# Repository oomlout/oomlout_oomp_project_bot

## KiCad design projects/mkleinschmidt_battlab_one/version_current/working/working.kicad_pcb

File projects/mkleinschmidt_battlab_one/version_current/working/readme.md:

# Battlab-One by mkleinschmidt  
This is a harvested standardized copy of a project from github.  
The original project can be found at:  
https://github.com/mkleinschmidt/Battlab-One  
Please consult that link for additional, details, files, and license information.  
Note: It was auto harvested and if the original repo had more than one board file or anything out of the ordinary the files here are likely not representative.

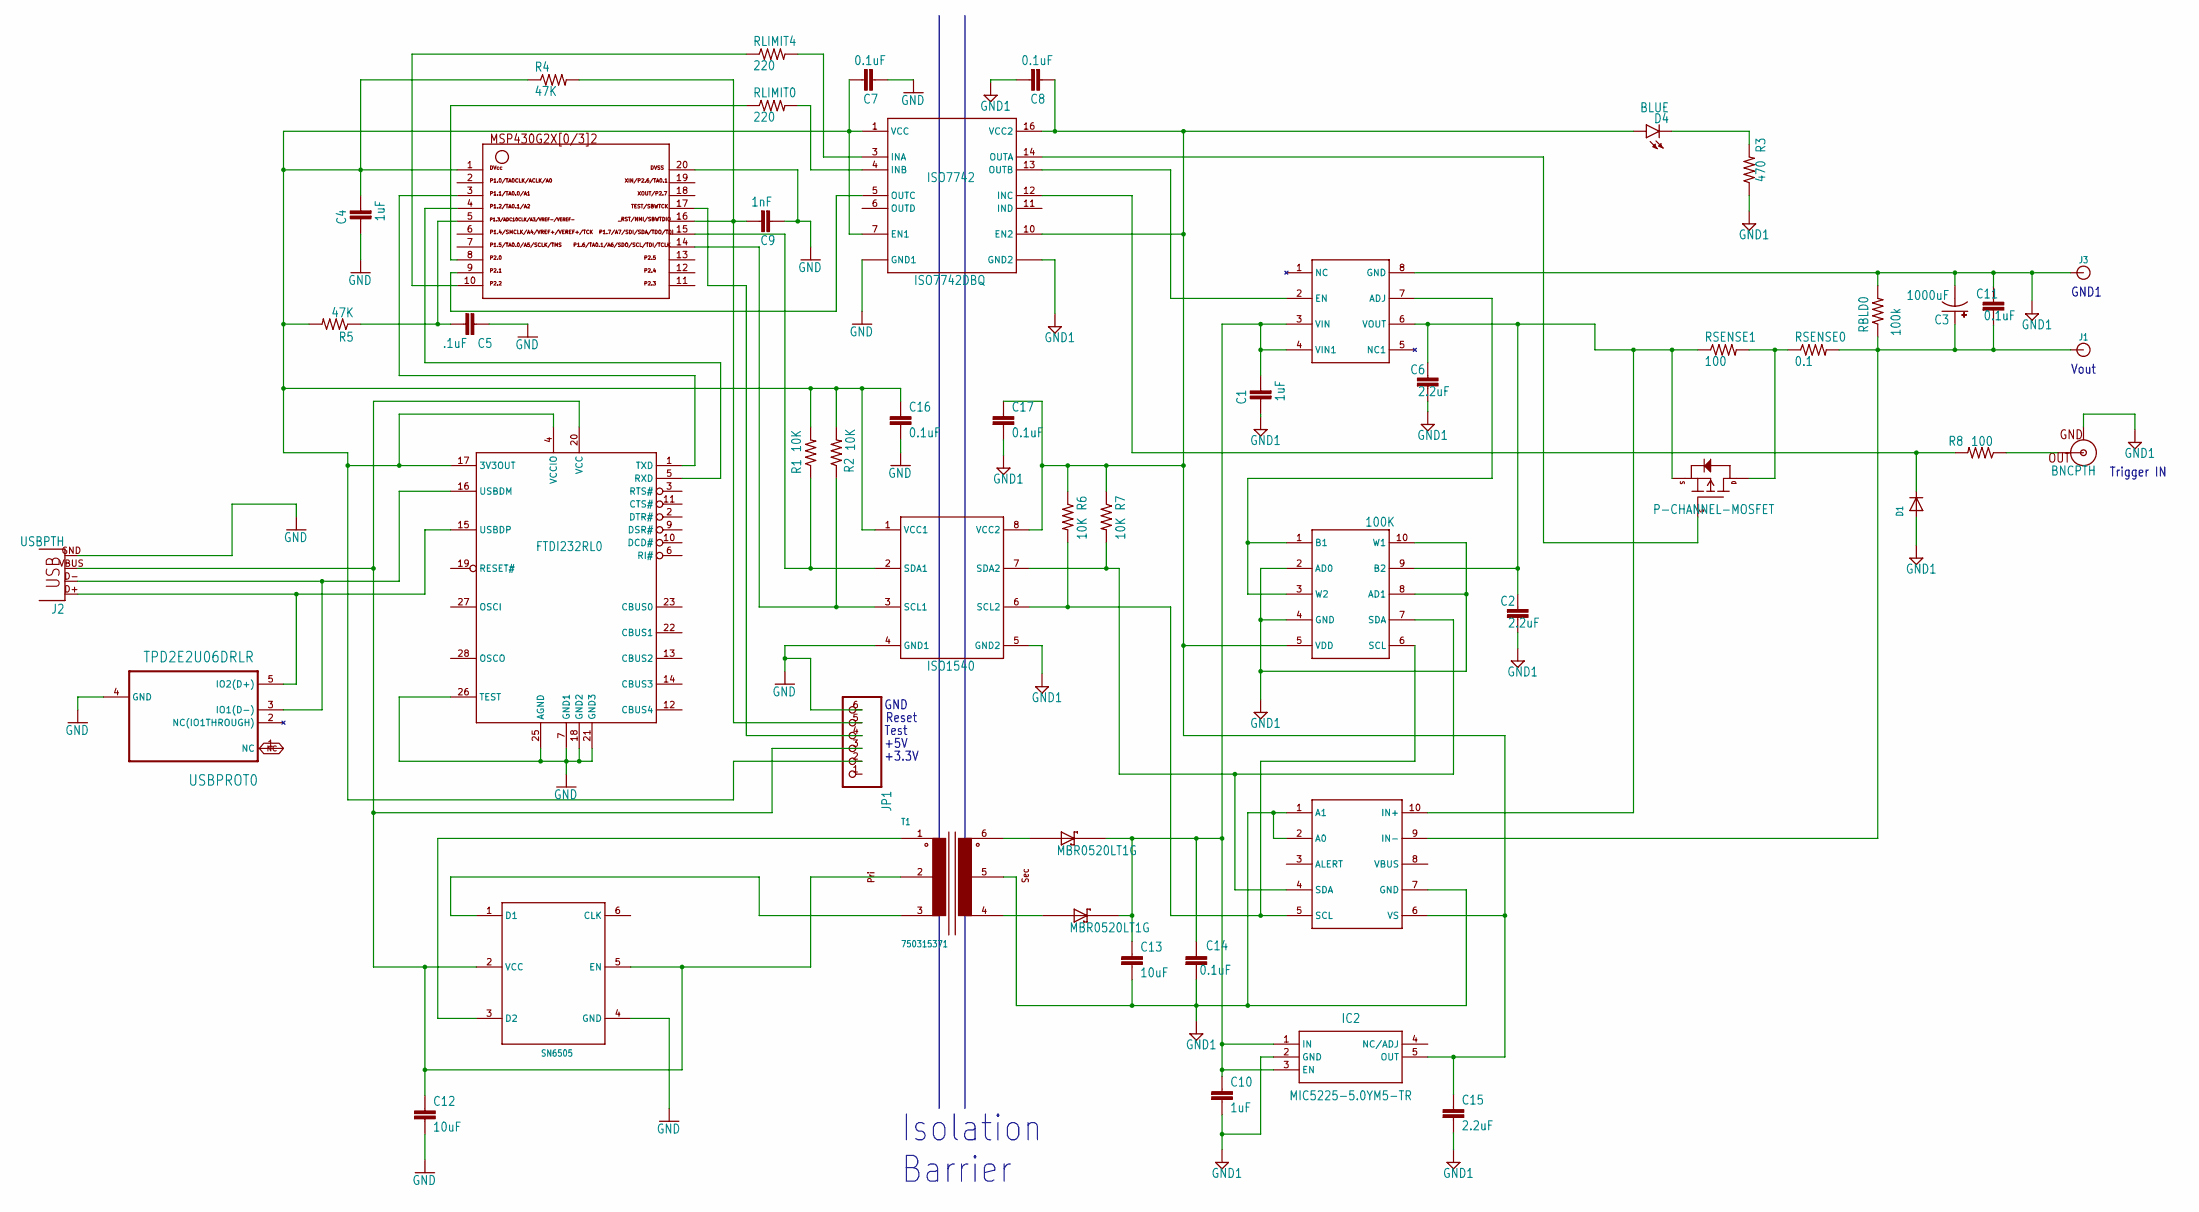
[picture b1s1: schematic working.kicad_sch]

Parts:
AD5248: 100K; MSOP-10
AP2318: AP2318; SOIC-8
C1, C4, C10: 1uF; 1206
C2, C6, C15: 2.2uF; 1206
C3: 1000uF; PANASONIC_F
C5: .1uF; 1206
C7, C8, C11, C14, C16, C17: 0.1uF; 1206
C9: 1nF; 1206
C12, C13: 10uF; 1206
D1: DIODESOD-123; SOD-123
D2, D3: MBR0520LT1G; SOD3716X117(SOD-123)
D4: BLUE; LED-1206
FTDI232RL0: FT232RL; SSOP28DB
IC2: MIC5225-5.0YM5-TR; SOT95P280X130-5N
INA233: INA233; VSSOP-10
ISO1540: ISO1540; SOIC127P600X175-8N
ISO7742: ISO7742DBQ; SOP63P599X175-16N
J1, J3: BANANA_CONN
J2: USBPTH; USB-B-PTH
JP1: PINHD-1X6; 1X06
MSP430: G2X[0/3]2---PW20; PW20
P-MOS0: P-CHANNEL-MOSFET; SOT23-3
R1, R2, R6, R7: 10K; 1206
R3: 470; 1206
R4, R5: 47K; 1206
R8: 100; 1206
RBLD0: 100k; 1206
RLIMIT0, RLIMIT4: 220; 1206
RSENSE0: 0.1; 1206
RSENSE1: 100; 1206
SN6505: SN6505; SOT95P280X145-6N
T1: 750315371; TOR-6P-HT4_SMT_6PIN_(1201)
TRIG0: BNCPTH; BNC
USBPROT0: TPD2E2U06DRLR; SOT50P160X60-5N

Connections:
3.3V: C4.2, C7.2, C16.1, FTDI232RL0.4 (VCCIO), FTDI232RL0.17 (3V3OUT), ISO1540.1 (VCC1), ISO7742.1 (VCC), ISO7742.7 (EN1), JP1.2, MSP430.1, R1.2, R2.2, R4.1, R5.2
+5V_LDO: AD5248.5 (VDD), C8.1, C15.1, C17.1, D4.A, IC2.5 (OUT), INA233.6 (VS), ISO1540.8 (VCC2), ISO7742.10 (EN2), ISO7742.16 (VCC2), R6.1, R7.1
GND: C4.1, C5.1, C7.1, C9.1, C12.2, C16.2, FTDI232RL0.7 (GND1), FTDI232RL0.18 (GND2), FTDI232RL0.21 (GND3), FTDI232RL0.25 (AGND), FTDI232RL0.26 (TEST), ISO1540.4 (GND1), ISO7742.2 (GND1), ISO7742.8 (GND1), J2.GND, JP1.6, MSP430.20, SN6505.4 (GND), USBPROT0.4 (GND)
GND1: AD5248.2 (AD0), AD5248.4 (GND), AD5248.8 (AD1), AD5248.10 (W1), AP2318.8 (GND), C1.1, C2.2, C3.-, C6.2, C8.2, C10.2, C11.1, C13.2, C14.2, C15.2, C17.2, D1.A, IC2.2 (GND), INA233.1 (A1), INA233.2 (A0), INA233.7 (GND), ISO1540.5 (GND2), ISO7742.9 (GND2), ISO7742.15 (GND2), J3.P$1, R3.1, RBLD0.2, T1.5, TRIG0.GND
LDO_EN: ISO7742.4 (INB), RLIMIT0.2
LDO_EN1: MSP430.8, RLIMIT0.1
LDO_EN2: AP2318.2 (EN), ISO7742.13 (OUTB)
unnamed: P-MOS0.3 (D), RSENSE0.1, RSENSE1.2
unnamed: AP2318.3 (VIN), AP2318.4 (VIN1), C1.2, C10.1, C13.1, C14.1, D2.1 (C), D3.1 (C), IC2.1 (IN), IC2.3 (EN)
unnamed: D3.2 (A), T1.4
unnamed: D2.2 (A), T1.6
unnamed: AD5248.1 (B1), AD5248.3 (W2), AP2318.7 (ADJ)
unnamed: D4.C, R3.2
unnamed: R8.1, TRIG0.S (OUT)
NC: USBPROT0.1 (NC)
RESET: C9.2, JP1.5, MSP430.16, R4.2
RS_EN: MSP430.10, RLIMIT4.1
RS_EN1: ISO7742.3 (INA), RLIMIT4.2
RS_EN2: ISO7742.14 (OUTA), P-MOS0.1 (G)
SCL1: ISO1540.3 (SCL1), MSP430.14, R2.1
SCL2: AD5248.6 (SCL), INA233.5 (SCL), ISO1540.6 (SCL2), R6.2
SDA1: ISO1540.2 (SDA1), MSP430.15, R1.1
SDA2: AD5248.7 (SDA), INA233.4 (SDA), ISO1540.7 (SDA2), R7.2
TEST: JP1.4, MSP430.17
TRANS1: SN6505.3 (D2), T1.1
TRANS3: SN6505.1 (D1), T1.3
TRIGGER_MSP1: ISO7742.5 (OUTC), MSP430.9
TRIGGER_MSP2: D1.C, ISO7742.12 (INC), R8.2
UART_RX: FTDI232RL0.5 (RXD), MSP430.4
UART_TX: FTDI232RL0.1 (TXD), MSP430.3
USB+: FTDI232RL0.15 (USBDP), J2.D+, USBPROT0.5 (IO2(D+))
USB-: FTDI232RL0.16 (USBDM), J2.D-, USBPROT0.3 (IO1(D-))
VBUS+5V: C12.1, FTDI232RL0.20 (VCC), J2.VBUS, JP1.3, SN6505.2 (VCC), SN6505.5 (EN), T1.2
VOUT: C3.+, C11.2, INA233.9 (IN-), J1.P$1, RBLD0.1, RSENSE0.2
VREF: C5.2, MSP430.5, R5.1
V_OUT: AD5248.9 (B2), AP2318.6 (VOUT), C2.1, C6.1, INA233.10 (IN+), P-MOS0.2 (S), RSENSE1.1

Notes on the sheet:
+5V
Reset
Trigger IN
GND
Vout
Isolation Barrier
Test
GND1
+3.3V

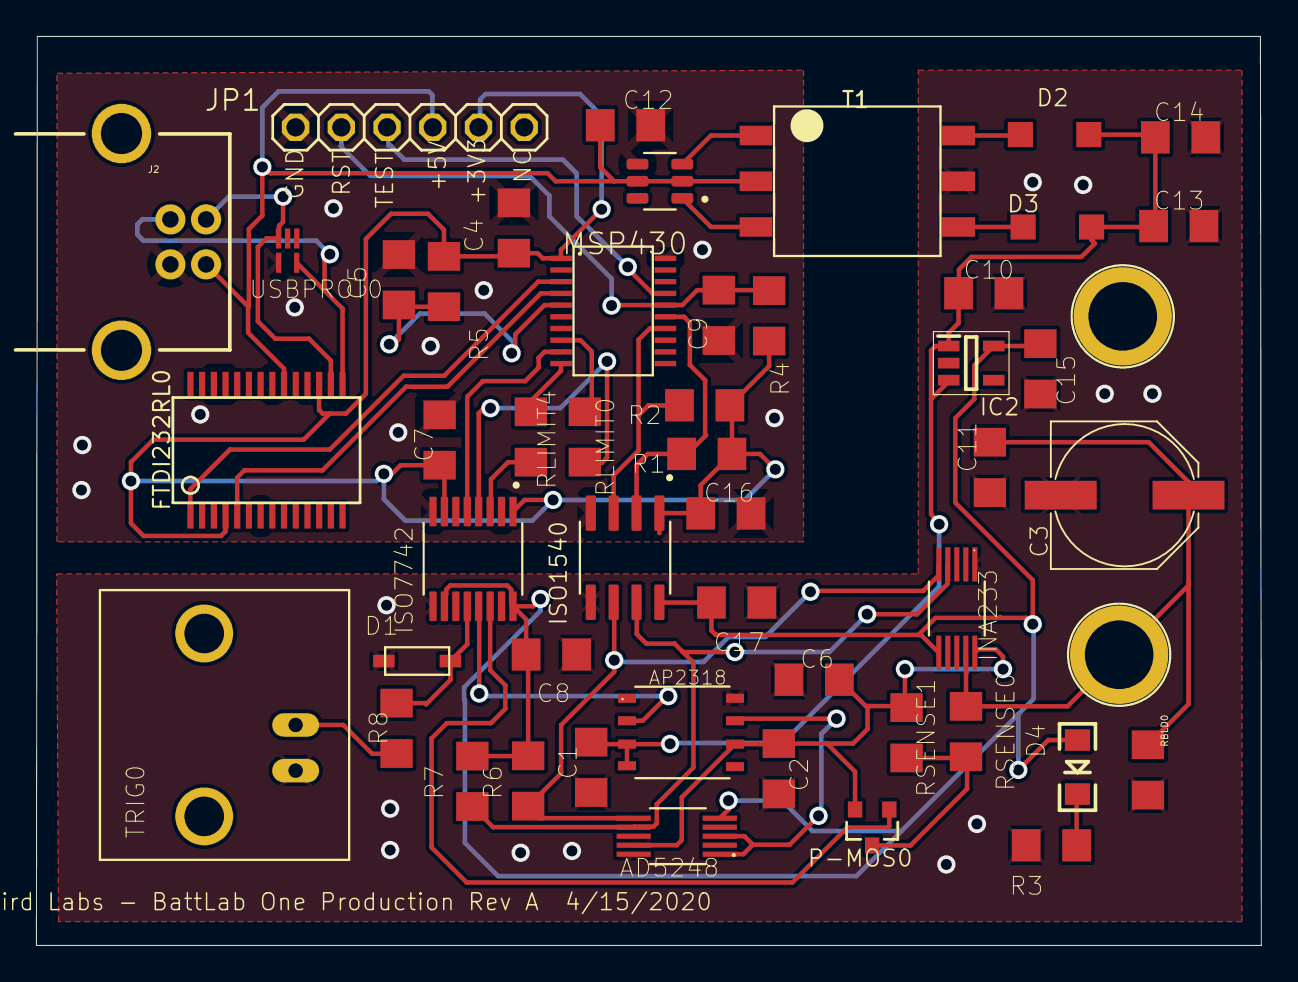
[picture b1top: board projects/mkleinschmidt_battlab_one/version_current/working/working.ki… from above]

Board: 2 copper layers, 68.1 x 50.5 mm, 51 parts (0 on the bottom side), 35 nets.

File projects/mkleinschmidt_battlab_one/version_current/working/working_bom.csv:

"Id";"Designator";"Footprint";"Quantity";"Designation";"Supplier and ref";
1;"C15,C2,C6";"1206";3;"2.2uF";;;
2;"C7,C14,C17,C8,C11,C16";"1206";6;"0.1uF";;;
3;"R8";"1206";1;"100";;;
4;"ISO1540";"SOIC127P600X175-8N";1;"ISO1540";;;
5;"C3";"PANASONIC_F";1;"1000uF";;;
6;"RLIMIT4,RLIMIT0";"1206";2;"220";;;
7;"C13,C12";"1206";2;"10uF";;;
8;"MSP430";"PW20";1;"MSP430";;;
9;"INA233";"VSSOP-10";1;"";;;
10;"C9";"1206";1;"1nF";;;
11;"D2,D3";"SOD3716X117(SOD-123)";2;"MBR0520LT1G";;;
12;"R3";"1206";1;"470";;;
13;"D4";"LED-1206";1;"BLUE";;;
14;"R6,R1,R7,R2";"1206";4;"10K";;;
15;"C10,C1,C4";"1206";3;"1uF";;;
16;"SN6505";"SOT95P280X145-6N";1;"SN6505";;;
17;"AD5248";"MSOP-10";1;"100K";;;
18;"AP2318";"SOIC-8";1;"";;;
19;"D1";"SOD-123";1;"";;;
20;"RSENSE1";"1206";1;"1000";;;
21;"TRIG0";"BNC";1;"BNCPTH";;;
22;"RSENSE0";"1206";1;"0.1";;;
23;"IC2";"SOT95P280X130-5N";1;"MIC5225-5.0YM5-TR";;;
24;"J2";"USB-B-PTH";1;"USB-B";;;
25;"P-MOS0";"SOT23-3";1;"P-MOSFET";;;
26;"J1,J3";"BANANA_CONN";2;"";;;
27;"JP1";"1X06";1;"";;;
28;"RBLD0";"1206";1;"100k";;;
29;"FTDI232RL0";"SSOP28DB";1;"";;;
30;"C5";"1206";1;".1uF";;;
31;"R4,R5";"1206";2;"47K";;;
32;"USBPROT0";"SOT50P160X60-5N";1;"TPD2E2U06DRLR";;;
33;"ISO7742";"SOP63P599X175-16N";1;"ISO7742DBQ";;;
34;"T1";"TOR-6P-HT4_SMT_6PIN_(1201)";1;"750315371";;;

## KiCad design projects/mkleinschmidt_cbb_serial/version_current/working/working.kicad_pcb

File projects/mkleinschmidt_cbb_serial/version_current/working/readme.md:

# CBB-Serial by mkleinschmidt  
This is a harvested standardized copy of a project from github.  
The original project can be found at:  
https://github.com/mkleinschmidt/CBB-Serial  
Please consult that link for additional, details, files, and license information.  
Note: It was auto harvested and if the original repo had more than one board file or anything out of the ordinary the files here are likely not representative.

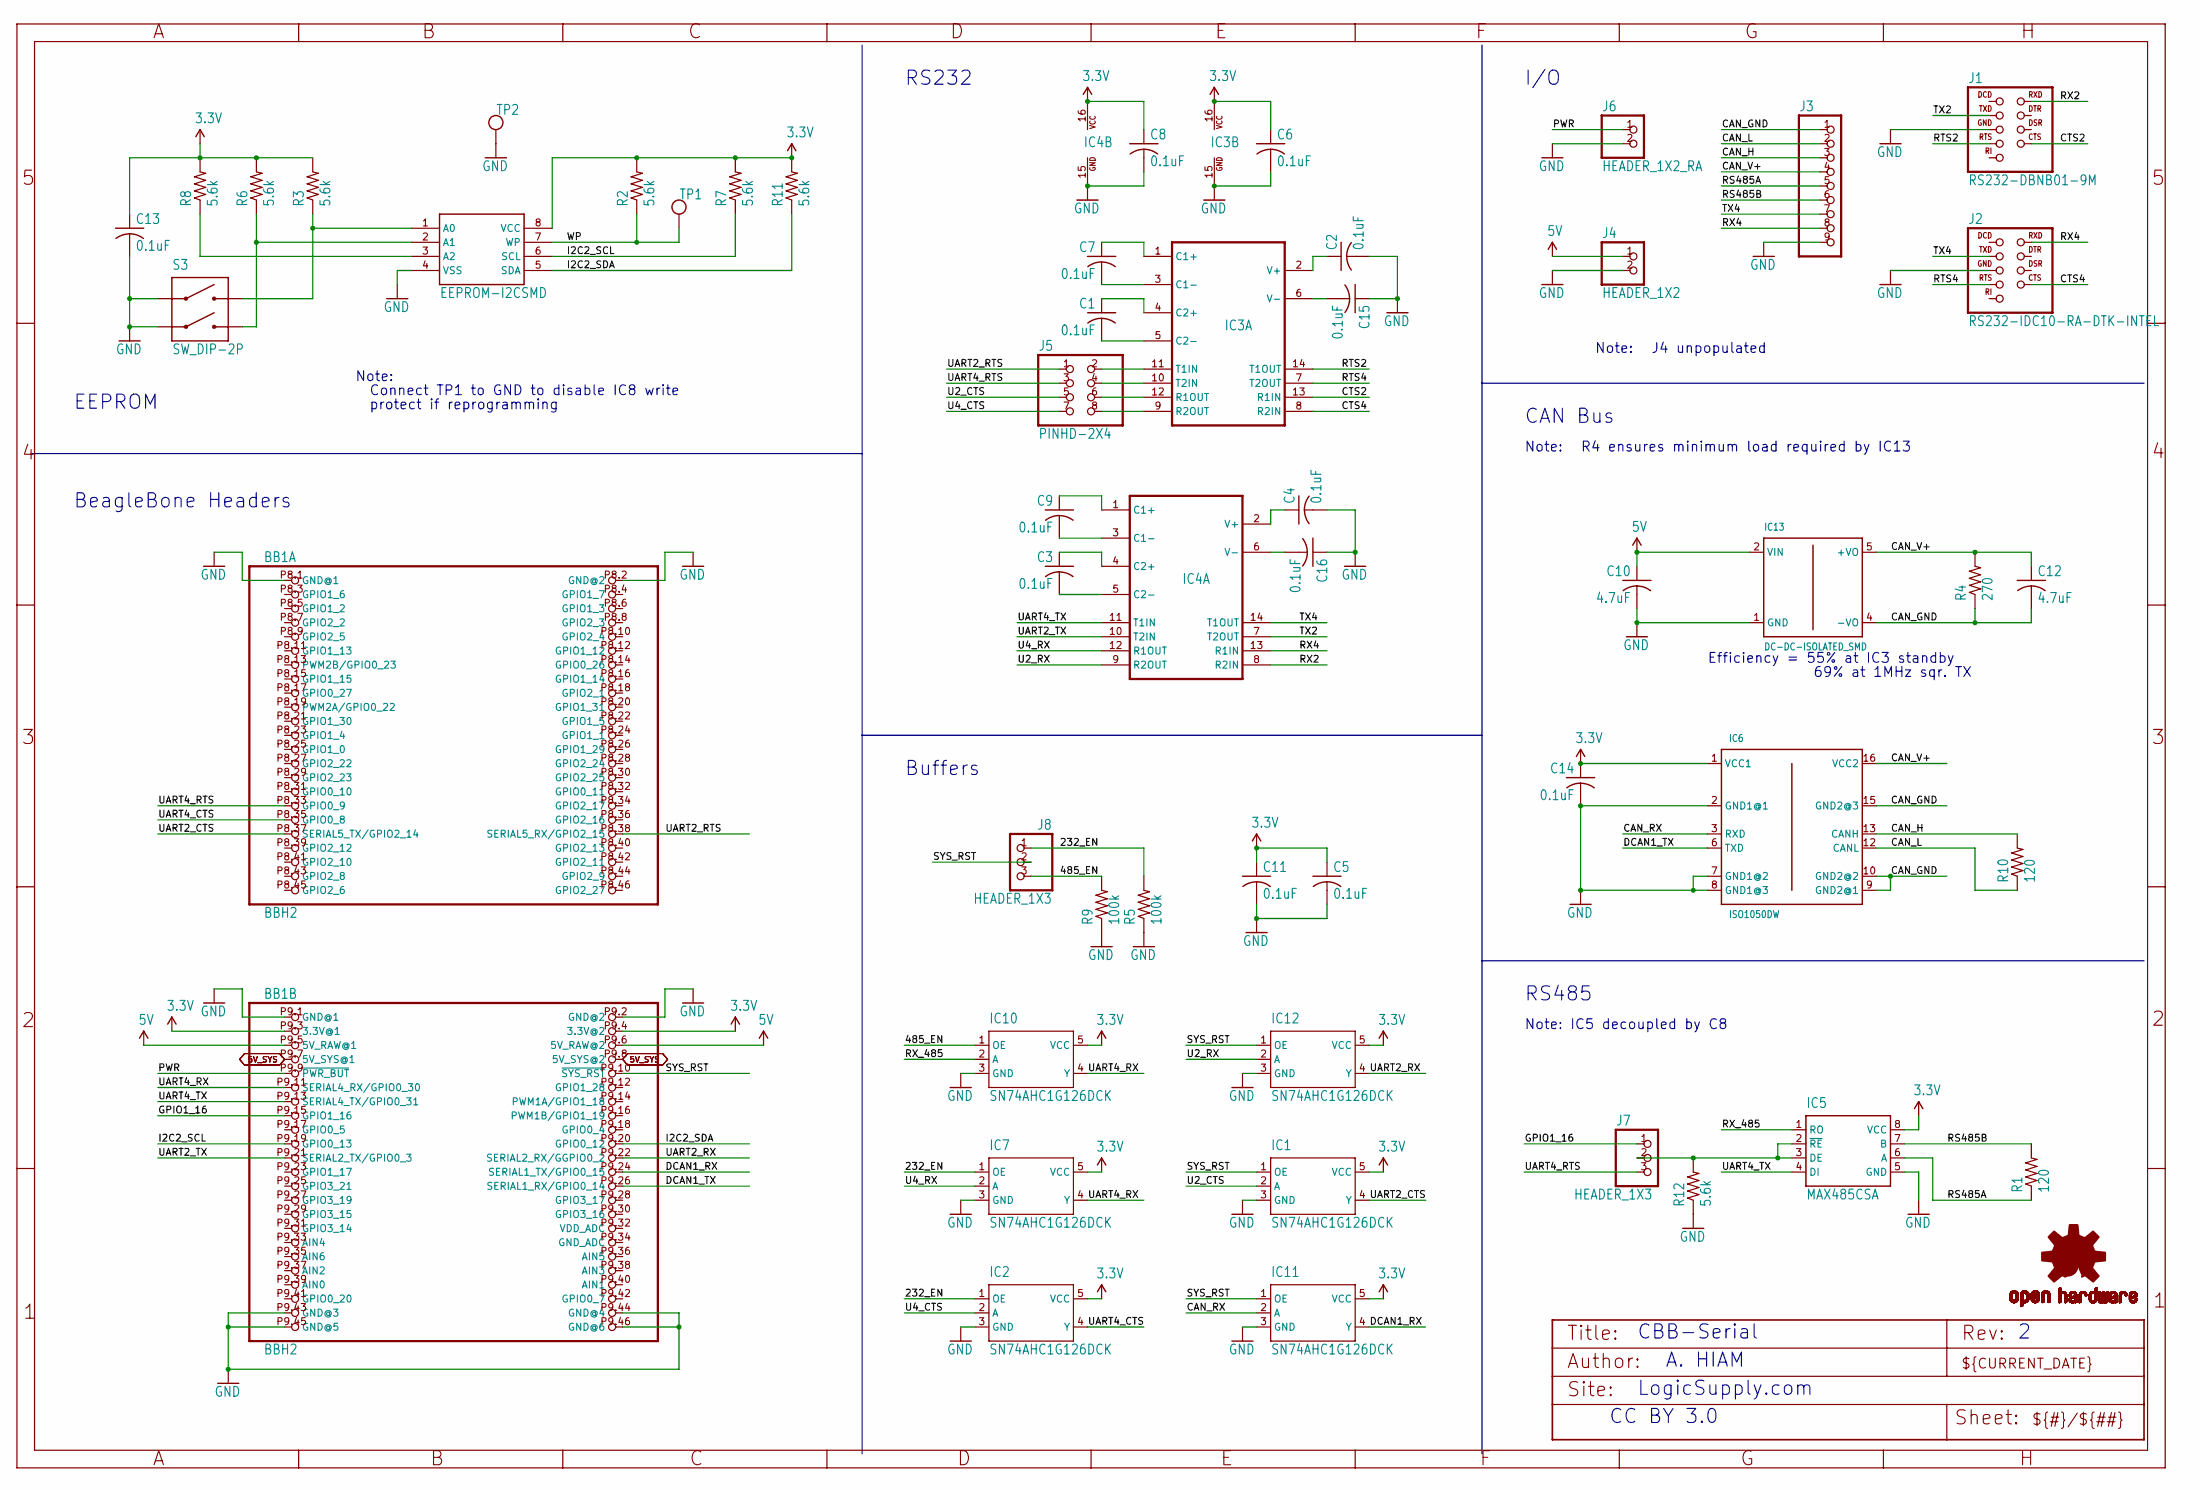
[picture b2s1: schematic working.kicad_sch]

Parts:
BB1: BBH2; BB_CAPE_TOP
C1, C2, C3, C4, C5, C6, C7, C8, C9, C11, C13, C14, C15, C16: 0.1uF; C0603
C10, C12: 4.7uF; C0805
IC1, IC2, IC7, IC10, IC11, IC12: SN74AHC1G126DCK; DCK-R-PDSO-G5
IC3, IC4: MAX3232UE; TSSOP16; MPN MAX3232CUE+
IC5: MAX485CSA; SO08
IC6: ISO1050DW; SO16W
IC8: EEPROM-I2CSMD; SO08
IC13: DC-DC-ISOLATED_SMD; DC-DC-SMD
J1: RS232-DBNB01-9M; DB9-DBNB01-9M
J2: RS232-IDC10-RA-DTK-INTEL; HEADER_2X5-SHROUDED-RA
J3: SCREWTERM_9PIN_2-54; SCREWTERM_1725724_9
J4: HEADER_1X2
J5: PINHD-2X4; HEADER_2X4
J6: HEADER_1X2_RA
J7, J8: HEADER_1X3
R1, R10: 120; R1206
R2, R3, R6, R7, R8, R11, R12: 5.6k; R0603
R4: 270; R1206
R5, R9: 100k; R0603
S3: SW_DIP-2P; DIPSWITCH-2P-SMD-1.27
TP1, TP2: TEST_POINT_PTH
U$7: OSHW-LOGOM; OSHW-LOGO-M

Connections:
3.3V: BB1.P9.3 (3.3V@1), BB1.P9.4 (3.3V@2), C5.1, C6.1, C8.1, C11.1, C13.1, C14.1, IC1.5 (VCC), IC2.5 (VCC), IC3.16 (VCC), IC4.16 (VCC), IC5.8 (VCC), IC6.1 (VCC1), IC7.5 (VCC), IC8.8 (VCC), IC10.5 (VCC), IC11.5 (VCC), IC12.5 (VCC), R2.2, R3.2, R6.2, R7.2, R8.2, R11.2
5V: BB1.P9.5 (5V_RAW@1), BB1.P9.6 (5V_RAW@2), C10.1, IC13.2 (VIN), J4.1
5V_SYS: BB1.P9.7 (5V_SYS@1), BB1.P9.8 (5V_SYS@2)
232_EN: IC2.1 (OE), IC7.1 (OE), J8.1, R5.2
485_EN: IC10.1 (OE), J8.3, R9.2
CAN_GND: C12.2, IC6.9 (GND2@1), IC6.10 (GND2@2), IC6.15 (GND2@3), IC13.4 (-VO), J3.1, R4.1
CAN_H: IC6.13 (CANH), J3.3, R10.2
CAN_L: IC6.12 (CANL), J3.2, R10.1
CAN_RX: IC6.3 (RXD), IC11.2 (A)
CAN_V+: C12.1, IC6.16 (VCC2), IC13.5 (+VO), J3.4, R4.2
CTS2: IC3.13 (R1IN), J1.8 (CTS)
CTS4: IC3.8 (R2IN), J2.6 (CTS)
DCAN1_RX: BB1.P9.24 (SERIAL1_TX/GPIO0_15), IC11.4 (Y)
DCAN1_TX: BB1.P9.26 (SERIAL1_RX/GPIO0_14), IC6.6 (TXD)
GND: BB1.P8.1 (GND@1), BB1.P8.2 (GND@2), BB1.P9.1 (GND@1), BB1.P9.2 (GND@2), BB1.P9.43 (GND@3), BB1.P9.44 (GND@4), BB1.P9.45 (GND@5), BB1.P9.46 (GND@6), C2.2, C4.2, C5.2, C6.2, C8.2, C10.2, C11.2, C13.2, C14.2, C15.1, C16.1, IC1.3 (GND), IC2.3 (GND), IC3.15 (GND), IC4.15 (GND), IC5.5 (GND), IC6.2 (GND1@1), IC6.7 (GND1@2), IC6.8 (GND1@3), IC7.3 (GND), IC8.4 (VSS), IC10.3 (GND), IC11.3 (GND), IC12.3 (GND), IC13.1 (GND), J1.5 (GND), J2.9 (GND), J3.9, J4.2, J6.2, R5.1, R9.1, R12.1, S3.1A, S3.2A, TP2.P$1
GPIO1_16: BB1.P9.15 (GPIO1_16), J7.1
I2C2_SCL: BB1.P9.19 (GPIO0_13), IC8.6 (SCL), R7.1
I2C2_SDA: BB1.P9.20 (GPIO0_12), IC8.5 (SDA), R11.1
unnamed: C9.2, IC4.3 (C1-)
unnamed: C3.2, IC4.5 (C2-)
unnamed: C9.1, IC4.1 (C1+)
unnamed: C3.1, IC4.4 (C2+)
unnamed: C16.2, IC4.6 (V-)
unnamed: C4.1, IC4.2 (V+)
unnamed: C15.2, IC3.6 (V-)
unnamed: C7.2, IC3.3 (C1-)
unnamed: IC5.2 (~RE), IC5.3 (DE), J7.2, R12.2
unnamed: C1.2, IC3.5 (C2-)
unnamed: C7.1, IC3.1 (C1+)
unnamed: C1.1, IC3.4 (C2+)
unnamed: IC8.1 (A0), R3.1, S3.1B
unnamed: IC8.2 (A1), R6.1, S3.2B
unnamed: IC8.3 (A2), R8.1
unnamed: C2.1, IC3.2 (V+)
unnamed: IC3.11 (T1IN), J5.2
unnamed: IC3.12 (R1OUT), J5.6
unnamed: IC3.10 (T2IN), J5.4
unnamed: IC3.9 (R2OUT), J5.8
PWR: BB1.P9.9 (~PWR_BUT), J6.1
RS485A: IC5.6 (A), J3.5, R1.1
RS485B: IC5.7 (B), J3.6, R1.2
RTS2: IC3.14 (T1OUT), J1.7 (RTS)
RTS4: IC3.7 (T2OUT), J2.4 (RTS)
RX2: IC4.8 (R2IN), J1.2 (RXD)
RX4: IC4.13 (R1IN), J2.3 (RXD), J3.8
RX_485: IC5.1 (RO), IC10.2 (A)
SYS_RST: BB1.P9.10 (~SYS_RST), IC1.1 (OE), IC11.1 (OE), IC12.1 (OE), J8.2
TX2: IC4.7 (T2OUT), J1.3 (TXD)
TX4: IC4.14 (T1OUT), J2.5 (TXD), J3.7
U2_CTS: IC1.2 (A), J5.5
U2_RX: IC4.9 (R2OUT), IC12.2 (A)
U4_CTS: IC2.2 (A), J5.7
U4_RX: IC4.12 (R1OUT), IC7.2 (A)
UART2_CTS: BB1.P8.37 (SERIAL5_TX/GPIO2_14), IC1.4 (Y)
UART2_RTS: BB1.P8.38 (SERIAL5_RX/GPIO2_15), J5.1
UART2_RX: BB1.P9.22 (SERIAL2_RX/GGPIO0_2), IC12.4 (Y)
UART2_TX: BB1.P9.21 (SERIAL2_TX/GPIO0_3), IC4.10 (T2IN)
UART4_CTS: BB1.P8.35 (GPIO0_8), IC2.4 (Y)
UART4_RTS: BB1.P8.33 (GPIO0_9), J5.3, J7.3
UART4_RX: BB1.P9.11 (SERIAL4_RX/GPIO0_30), IC7.4 (Y), IC10.4 (Y)
UART4_TX: BB1.P9.13 (SERIAL4_TX/GPIO0_31), IC4.11 (T1IN), IC5.4 (DI)
WP: IC8.7 (WP), R2.1, TP1.P$1

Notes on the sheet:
EEPROM
Buffers
I/O
CAN Bus
BeagleBone Headers
A. HIAM
J4 unpopulated
LogicSupply.com
protect if reprogramming
R4 ensures minimum load required by IC13
CC BY 3.0
CBB-Serial
69% at 1MHz sqr. TX
Note:
Connect TP1 to GND to disable IC8 write
Efficiency = 55% at IC3 standby
Note: IC5 decoupled by C8
RS485
RS232

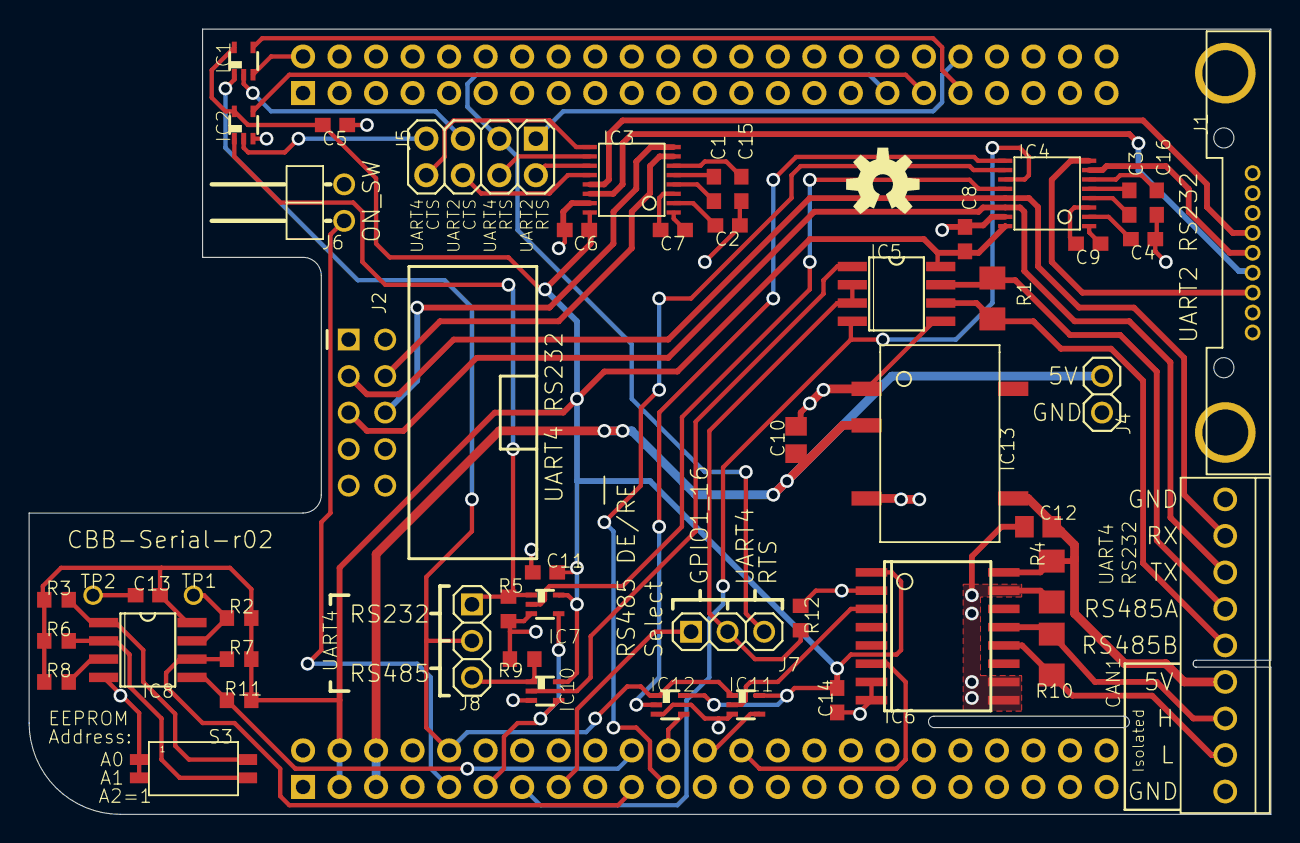
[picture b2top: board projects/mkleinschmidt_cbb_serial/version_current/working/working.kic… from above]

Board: 2 copper layers, 86.4 x 54.6 mm, 53 parts (1 on the bottom side), 62 nets.

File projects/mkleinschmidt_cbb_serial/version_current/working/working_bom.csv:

"Id";"Designator";"Footprint";"Quantity";"Designation";"Supplier and ref";
1;"C5,C16,C15,C14,C2,C8,C7,C13,C6,C11,C4,C9,C3,C1";"C0603";14;"0.1uF";;;
2;"TP2,TP1";"TEST_POINT_PTH";2;"TEST_POINT_PTH";;;
3;"R9,R5";"R0603";2;"100k";;;
4;"IC13";"DC-DC-SMD";1;"DC-DC-ISOLATED_SMD";;;
5;"J3";"SCREWTERM_1725724_9";1;"SCREWTERM_9PIN_2-54";;;
6;"IC7,IC1,IC12,IC11,IC2,IC10";"DCK-R-PDSO-G5";6;"SN74AHC1G126DCK";;;
7;"IC6";"SO16W";1;"ISO1050DW";;;
8;"R3,R8,R6,R7,R11,R2,R12";"R0603";7;"5.6k";;;
9;"J2";"HEADER_2X5-SHROUDED-RA";1;"RS232-IDC10-RA-DTK-INTEL";;;
10;"IC8";"SO08";1;"EEPROM-I2CSMD";;;
11;"J5";"HEADER_2X4";1;"PINHD-2X4";;;
12;"IC5";"SO08";1;"MAX485CSA";;;
13;"J7,J8";"HEADER_1X3";2;"HEADER_1X3";;;
14;"IC4,IC3";"TSSOP16";2;"MAX3232CUE";;;
15;"C12,C10";"C0805";2;"4.7uF";;;
16;"R1,R10";"R1206";2;"120";;;
17;"J6";"HEADER_1X2_RA";1;"HEADER_1X2_RA";;;
18;"S3";"DIPSWITCH-2P-SMD-1.27";1;"SW_DIP-2P";;;
19;"U$7";"OSHW-LOGO-M";1;"OSHW-LOGOM";;;
20;"R4";"R1206";1;"270";;;
21;"J4";"HEADER_1X2";1;"HEADER_1X2";;;
22;"J1";"DB9-DBNB01-9M";1;"RS232-DBNB01-9M";;;
23;"BB1";"BB_CAPE_TOP";1;"BBH2";;;

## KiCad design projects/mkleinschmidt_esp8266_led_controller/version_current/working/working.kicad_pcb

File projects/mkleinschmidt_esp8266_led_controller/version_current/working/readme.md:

# OOMP Project  
## ESP8266_LED_Controller  by mkleinschmidt  
  
oomp key: oomp_projects_flat_mkleinschmidt_esp8266_led_controller  
(snippet of original readme)  

  full source readme at [readme_src.md](readme_src.md)  
  
source repo at: [https://github.com/mkleinschmidt/ESP8266_LED_Controller](https://github.com/mkleinschmidt/ESP8266_LED_Controller)  
## Board  

## Schematic  

[schematic pdf](working_schematic.pdf)  
## Images

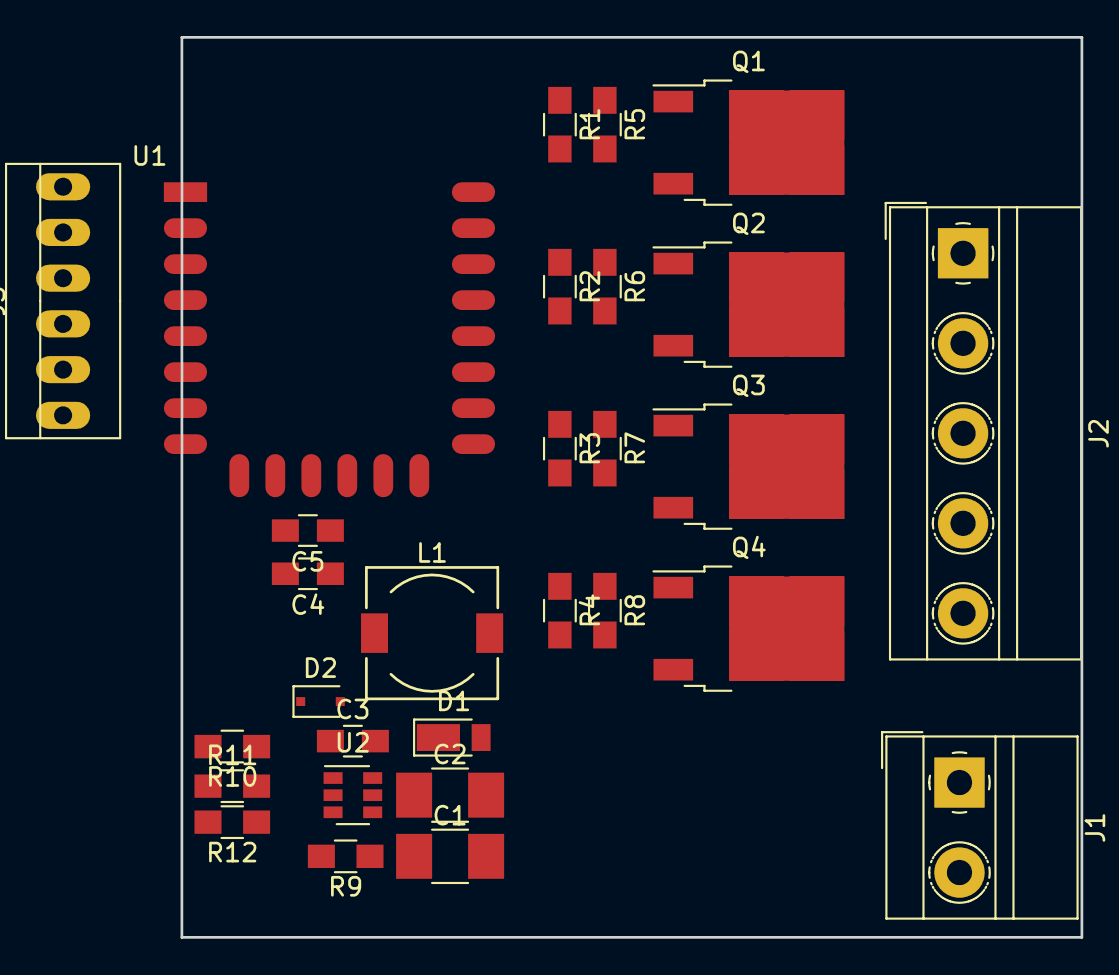
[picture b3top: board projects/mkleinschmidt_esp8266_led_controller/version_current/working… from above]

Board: 2 copper layers, 50.0 x 50.0 mm, 29 parts (0 on the bottom side), 22 nets, no tracks yet.

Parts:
C1, C2: 4.7uF; C_1210_HandSoldering
C3: 100nF; C_0805_HandSoldering
C4, C5: 10uF; C_0805_HandSoldering
D1: D_Schottky_Small; D_PowerDI-123
D2: D_Small; D_SOD-323F
J1: Screw_Terminal_01x02; TerminalBlock_MetzConnect_Type011_RT05502HBWC_Pitch5.00mm
J2: Screw_Terminal_01x05; TerminalBlock_MetzConnect_Type011_RT05505HBWC_Pitch5.00mm
J3: Conn_01x06; PINHEAD1-6
L1: 15uH; Choke_SMD_7.3x7.3_H4.5
Q1, Q2, Q3, Q4: Q_NMOS_GDS; TO-252-2
R1, R2, R3, R4, R10: 10; R_0805_HandSoldering
R5, R6, R7, R8: 100k; R_0805_HandSoldering
R9: 1M; R_0805_HandSoldering
R11: 31.6k; R_0805_HandSoldering
R12: 10k; R_0805_HandSoldering
U1: ESP-12E
U2: MCP16301; SOT-23-6

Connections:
+3V3: C4.1, C5.1, D2.2, L1.1, R10.1, U1.8
GND: C1.2, C2.2, C4.2, C5.2, D1.2, J1.2, J3.1, Q1.3, Q2.3, Q3.3, Q4.3, R5.2, R6.2, R7.2, R8.2, R12.2, U1.15, U2.2
unnamed: C3.1, D2.1, U2.1
unnamed: C3.2, D1.1, L1.2, U2.6
unnamed: J2.1, Q1.2
unnamed: J2.2, Q2.2
unnamed: J2.3, Q3.2
unnamed: J2.4, Q4.2
unnamed: J3.4, U1.22
unnamed: J3.5, U1.21
unnamed: Q1.1, R1.1, R5.1
unnamed: Q2.1, R2.1, R6.1
unnamed: Q3.1, R3.1, R7.1
unnamed: Q4.1, R4.1, R8.1
unnamed: R1.2, U1.20
unnamed: R2.2, U1.19
unnamed: R3.2, U1.18
unnamed: R4.2, U1.17
unnamed: R9.2, U2.4
unnamed: R10.2, R11.1
unnamed: R11.2, R12.1, U2.3
VDD: C1.1, C2.1, J1.1, J2.5, R9.1, U2.5

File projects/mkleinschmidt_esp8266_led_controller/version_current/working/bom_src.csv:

"Source:","D:/Home/privat/Fablab/Projekte/ESP8266_LED/KiCAD/LEDController.sch"
"Date:","12/04/2018 10:26:57"
"Tool:","Eeschema 4.0.7"
"Generator:","C:/Program Files/KiCad/bin/scripting/plugins/bom_csv_grouped_by_value.py"
"Component Count:","28"

"Individual Components:"

"Item","Qty","Reference(s)","Value","LibPart","Footprint","Datasheet","Mouser-Nr.","Reichelt Artikel-Nr."
"","","C1","4.7uF","device:C_Small","Capacitors_SMD:C_1210_HandSoldering","","81-GRM32R71H475KA88L","X7R-G1210 4,7"
"","","C2","4.7uF","device:C_Small","Capacitors_SMD:C_1210_HandSoldering","","81-GRM32R71H475KA88L","X7R-G1210 4,7"
"","","C3","100nF","device:C_Small","Capacitors_SMD:C_0805_HandSoldering","","581-08055C104K","X7R-G0805 100N"
"","","C4","10uF","device:C_Small","Capacitors_SMD:C_0805_HandSoldering","","810-C2012X7R1A106K","X7R 0805 CB 10U"
"","","C5","10uF","device:C_Small","Capacitors_SMD:C_0805_HandSoldering","","810-C2012X7R1A106K","X7R 0805 CB 10U"
"","","D1","D_Schottky_Small","device:D_Schottky_Small","Diodes_SMD:D_PowerDI-123","","",""
"","","D2","D_Small","device:D_Small","Diodes_SMD:D_SOD-323F","","621-1N4148WQ-7-F","1N 4148W7F DII"
"","","J1","Screw_Terminal_01x02","conn:Screw_Terminal_01x02","TerminalBlock_MetzConnect:TerminalBlock_MetzConnect_Type011_RT05502HBWC_Pitch5.00mm","","","AKL 012-02"
"","","J2","Screw_Terminal_01x05","conn:Screw_Terminal_01x05","TerminalBlock_MetzConnect:TerminalBlock_MetzConnect_Type011_RT05505HBWC_Pitch5.00mm","","",""
"","","J3","Conn_01x06","conn:Conn_01x06","Connectors:PINHEAD1-6","","",""
"","","L1","15uH","device:L_Small","Choke_SMD:Choke_SMD_7.3x7.3_H4.5","","",""
"","","Q1","Q_NMOS_GDS","device:Q_NMOS_GDS","TO_SOT_Packages_SMD:TO-252-2","","",""
"","","Q2","Q_NMOS_GDS","device:Q_NMOS_GDS","TO_SOT_Packages_SMD:TO-252-2","","",""
"","","Q3","Q_NMOS_GDS","device:Q_NMOS_GDS","TO_SOT_Packages_SMD:TO-252-2","","",""
"","","Q4","Q_NMOS_GDS","device:Q_NMOS_GDS","TO_SOT_Packages_SMD:TO-252-2","","",""
"","","R1","10","device:R_Small","Resistors_SMD:R_0805_HandSoldering","","",""
"","","R2","10","device:R_Small","Resistors_SMD:R_0805_HandSoldering","","",""
"","","R3","10","device:R_Small","Resistors_SMD:R_0805_HandSoldering","","",""
"","","R4","10","device:R_Small","Resistors_SMD:R_0805_HandSoldering","","",""
"","","R5","100k","device:R_Small","Resistors_SMD:R_0805_HandSoldering","","",""
"","","R6","100k","device:R_Small","Resistors_SMD:R_0805_HandSoldering","","",""
"","","R7","100k","device:R_Small","Resistors_SMD:R_0805_HandSoldering","","",""
"","","R8","100k","device:R_Small","Resistors_SMD:R_0805_HandSoldering","","",""
"","","R9","1M","device:R_Small","Resistors_SMD:R_0805_HandSoldering","","603-RC0805FR-071ML","SMD-0805 1,00M"
"","","R11","31.2k","device:R_Small","Resistors_SMD:R_0805_HandSoldering","","",""
"","","R12","10k","device:R_Small","Resistors_SMD:R_0805_HandSoldering","","",""
"","","U1","ESP-12E","ESP8266:ESP-12E","ESP8266:ESP-12E","","",""
"","","U2","MCP16301","dc-dc:MCP16301","TO_SOT_Packages_SMD:SOT-23-6","","579-MCP16301T-I/CHY","MCP 16301T-I/CHY"



"Collated Components:"

"Item","Qty","Reference(s)","Value","LibPart","Footprint","Datasheet","Mouser-Nr.","Reichelt Artikel-Nr."
"1","2","C1, C2","4.7uF","device:C_Small","Capacitors_SMD:C_1210_HandSoldering","","81-GRM32R71H475KA88L","X7R-G1210 4,7"
"2","1","C3","100nF","device:C_Small","Capacitors_SMD:C_0805_HandSoldering","","581-08055C104K","X7R-G0805 100N"
"3","2","C4, C5","10uF","device:C_Small","Capacitors_SMD:C_0805_HandSoldering","","810-C2012X7R1A106K","X7R 0805 CB 10U"
"4","1","D1","D_Schottky_Small","device:D_Schottky_Small","Diodes_SMD:D_PowerDI-123","","",""
"5","1","D2","D_Small","device:D_Small","Diodes_SMD:D_SOD-323F","","621-1N4148WQ-7-F","1N 4148W7F DII"
"6","1","J1","Screw_Terminal_01x02","conn:Screw_Terminal_01x02","TerminalBlock_MetzConnect:TerminalBlock_MetzConnect_Type011_RT05502HBWC_Pitch5.00mm","","","AKL 012-02"
"7","1","J2","Screw_Terminal_01x05","conn:Screw_Terminal_01x05","TerminalBlock_MetzConnect:TerminalBlock_MetzConnect_Type011_RT05505HBWC_Pitch5.00mm","","",""
"8","1","J3","Conn_01x06","conn:Conn_01x06","Connectors:PINHEAD1-6","","",""
"9","1","L1","15uH","device:L_Small","Choke_SMD:Choke_SMD_7.3x7.3_H4.5","","",""
"10","4","Q1, Q2, Q3, Q4","Q_NMOS_GDS","device:Q_NMOS_GDS","TO_SOT_Packages_SMD:TO-252-2","","",""
"11","4","R1, R2, R3, R4","10","device:R_Small","Resistors_SMD:R_0805_HandSoldering","","",""
"12","4","R5, R6, R7, R8","100k","device:R_Small","Resistors_SMD:R_0805_HandSoldering","","",""
"13","1","R9","1M","device:R_Small","Resistors_SMD:R_0805_HandSoldering","","603-RC0805FR-071ML","SMD-0805 1,00M"
"14","1","R11","31.2k","device:R_Small","Resistors_SMD:R_0805_HandSoldering","","",""
"15","1","R12","10k","device:R_Small","Resistors_SMD:R_0805_HandSoldering","","",""
"16","1","U1","ESP-12E","ESP8266:ESP-12E","ESP8266:ESP-12E","","",""
"17","1","U2","MCP16301","dc-dc:MCP16301","TO_SOT_Packages_SMD:SOT-23-6","","579-MCP16301T-I/CHY","MCP 16301T-I/CHY"

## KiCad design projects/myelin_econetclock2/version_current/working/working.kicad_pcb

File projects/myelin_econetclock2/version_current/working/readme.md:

# EconetClock2 by myelin  
This is a harvested standardized copy of a project from github.  
The original project can be found at:  
https://github.com/myelin/EconetClock2  
Please consult that link for additional, details, files, and license information.  
Note: It was auto harvested and if the original repo had more than one board file or anything out of the ordinary the files here are likely not representative.

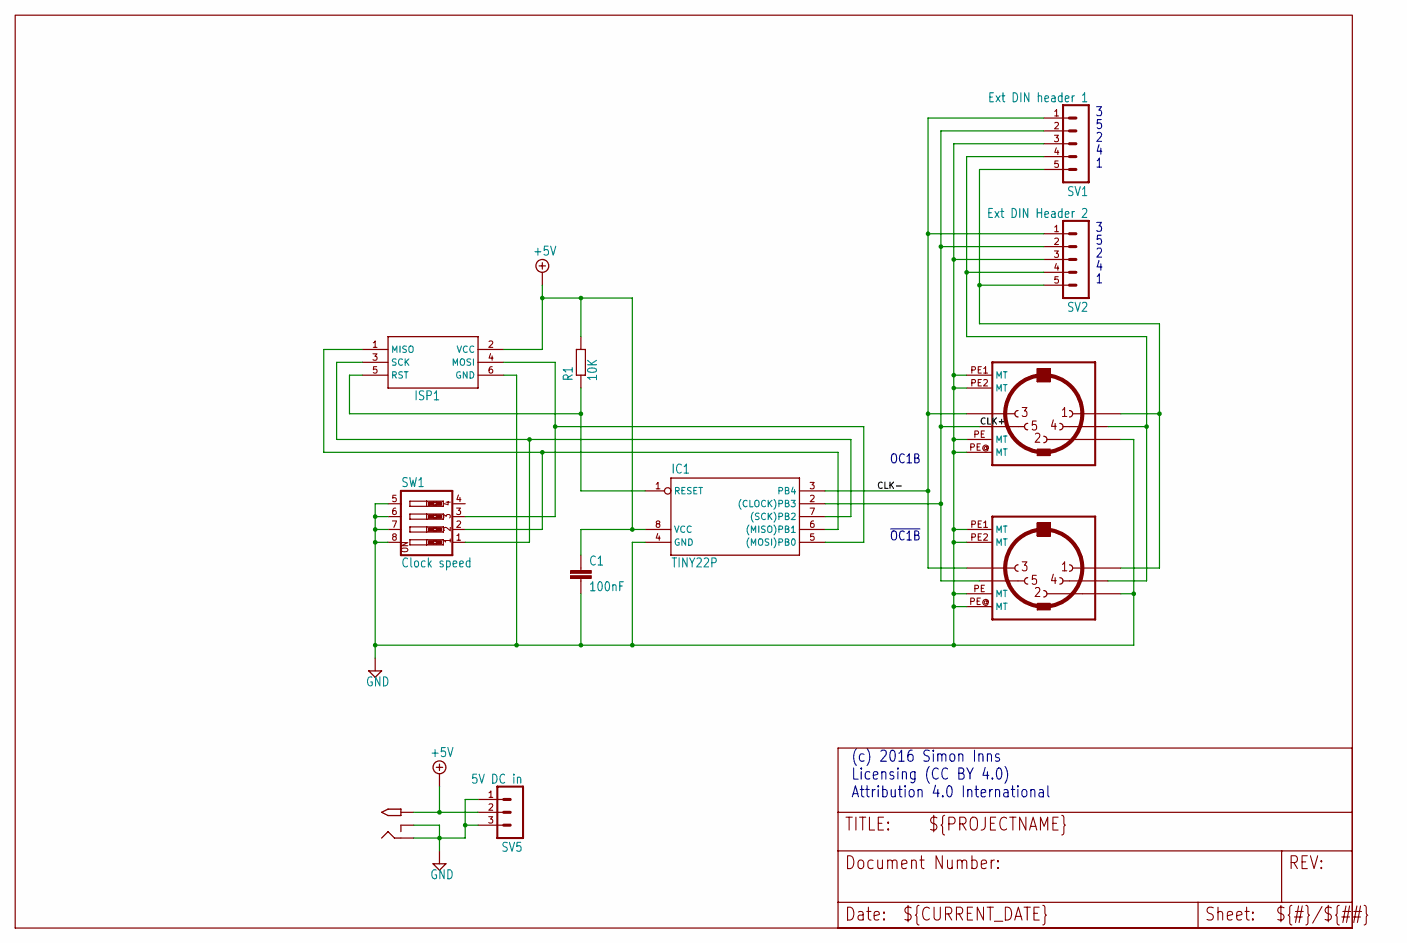
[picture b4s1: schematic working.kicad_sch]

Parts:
C1: 100nF; C050-025X075
DCJACK1: 2.1MMJACKTHM; PJ-102A
IC1: TINY22P; DIL08
ISP1: AVRISP-6; AVRISP
R1: 10K; 0204_7
SV1: Ext DIN header 1; MA05-1
SV2: Ext DIN Header 2; MA05-1
SV3, SV4: MIDIJACK; CP-2350
SV5: 5V DC in; MA03-1
SW1: Clock speed; EDG-04

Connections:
+5V: C1.1, DCJACK1.TIP, IC1.8 (VCC), ISP1.2 (VCC), R1.2, SV5.2
CLK+: IC1.2 ((CLOCK)PB3), SV1.2, SV2.2, SV3.5, SV4.5
CLK-: IC1.3 (PB4), SV1.1, SV2.1, SV3.3, SV4.3
GND: C1.2, DCJACK1.RING, DCJACK1.RING_SW, IC1.4 (GND), ISP1.6 (GND), SV1.3, SV2.3, SV3.2, SV3.PE (MT), SV3.PE1 (MT), SV3.PE2 (MT), SV3.PE@ (MT), SV4.2, SV4.PE (MT), SV4.PE1 (MT), SV4.PE2 (MT), SV4.PE@ (MT), SV5.1, SV5.3, SW1.5, SW1.6, SW1.7, SW1.8
unnamed: IC1.5 ((MOSI)PB0), ISP1.4 (MOSI), SW1.3
unnamed: IC1.7 ((SCK)PB2), ISP1.3 (SCK), SW1.1
unnamed: SV1.4, SV2.4, SV3.4, SV4.4
unnamed: IC1.6 ((MISO)PB1), ISP1.1 (MISO), SW1.2
unnamed: IC1.1 (RESET), ISP1.5 (RST), R1.1
unnamed: SV1.5, SV2.5, SV3.1, SV4.1

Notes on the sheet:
OC1B
(c) 2016 Simon Inns Licensing (CC BY 4.0) Attribution 4.0 International
~{OC1B}

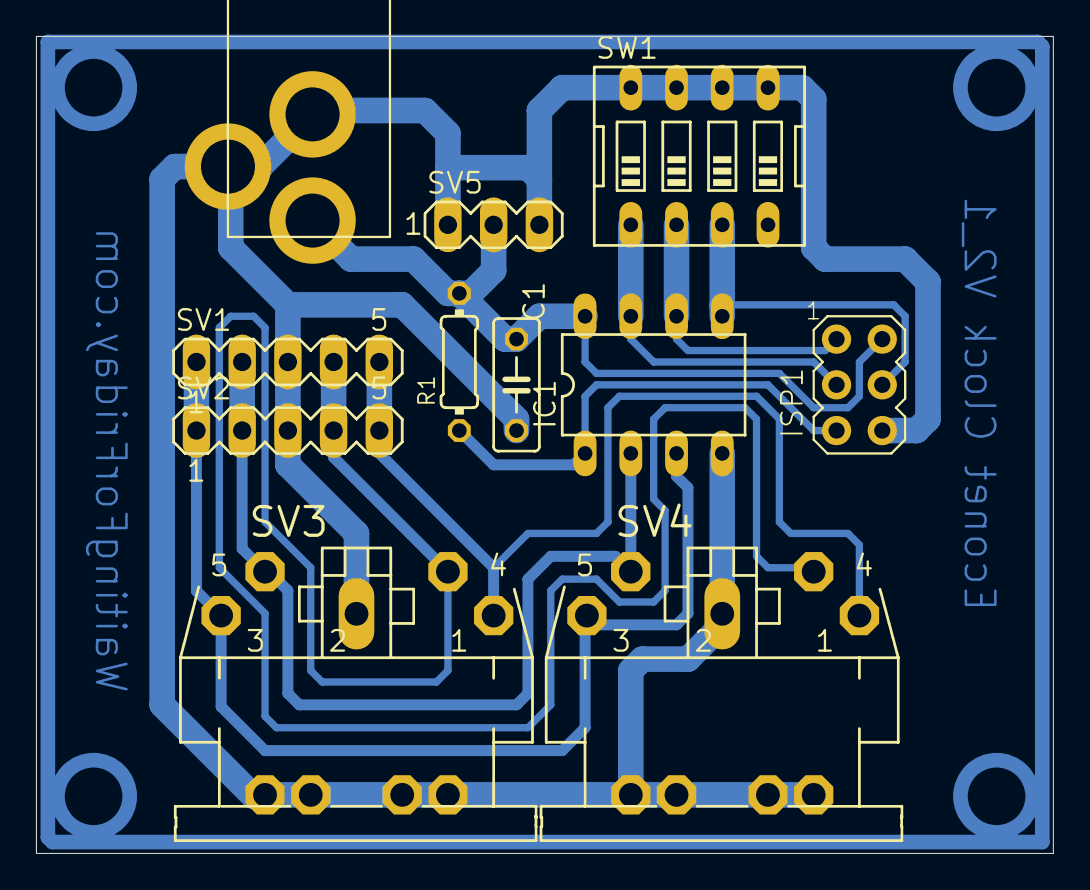
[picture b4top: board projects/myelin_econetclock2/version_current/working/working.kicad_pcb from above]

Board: 4 copper layers, 56.5 x 45.4 mm, 11 parts (0 on the bottom side), 10 nets.

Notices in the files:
projects/nathanjp91_nrf8001_breakout_board/version_current/working/working.kicad_pcb:
CC-BY-SA
projects/natsfr_greenlight/version_current/working/working.kicad_pcb:
CC-BY-SA-NC
